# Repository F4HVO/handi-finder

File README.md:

# handi-finder
F4HVO implementation of Handi Finder.

This circuit was made in a hurry but fortunately it works.

## How to make it

- Send the gerber files to your favorite PCB factory (OSH Park, Elecrow, AllPCB, ...).
- Get the components (see BOM below)
- Assemble (hot air station or reflow oven recommended, but a frying pan and sand can do the trick)
- Then add antennas : rigid wire of 48cm on each side, between ANT1 and ANT1GND (and ANT2-ANT2GND respectively). Make a bow shape by bending the wire to form 3 edges (two of 17cm and one of 12cm).
- Have fun.

## BOM
All capacitors and resistors are 0805.

- U1 : CD4047 (smd version)
- C1 : 0.2 uF
- C2, C3, C4, C5, C6, C7 : 1nF
- C8 : 0.1 uF
- R1, R2, R3 : 10k
- D1, D2 : 1n4148 (or any switching diode, or PIN diode)
- Switch : good luck, or no switch
- SMA connector
- 9V battery (and connector)

## Remarks

- The switch package is unfamiliar, a more standard one might be better. I did not use a switch, I soldered a jumper on my assembled board.

## Release notes

### Version 1.1 :
- Change diodes package to SOD 123
- Change hole diameter to 2.6mm

### Version 1.2 :
- Fix switch connection, CD4047 was always powered on.

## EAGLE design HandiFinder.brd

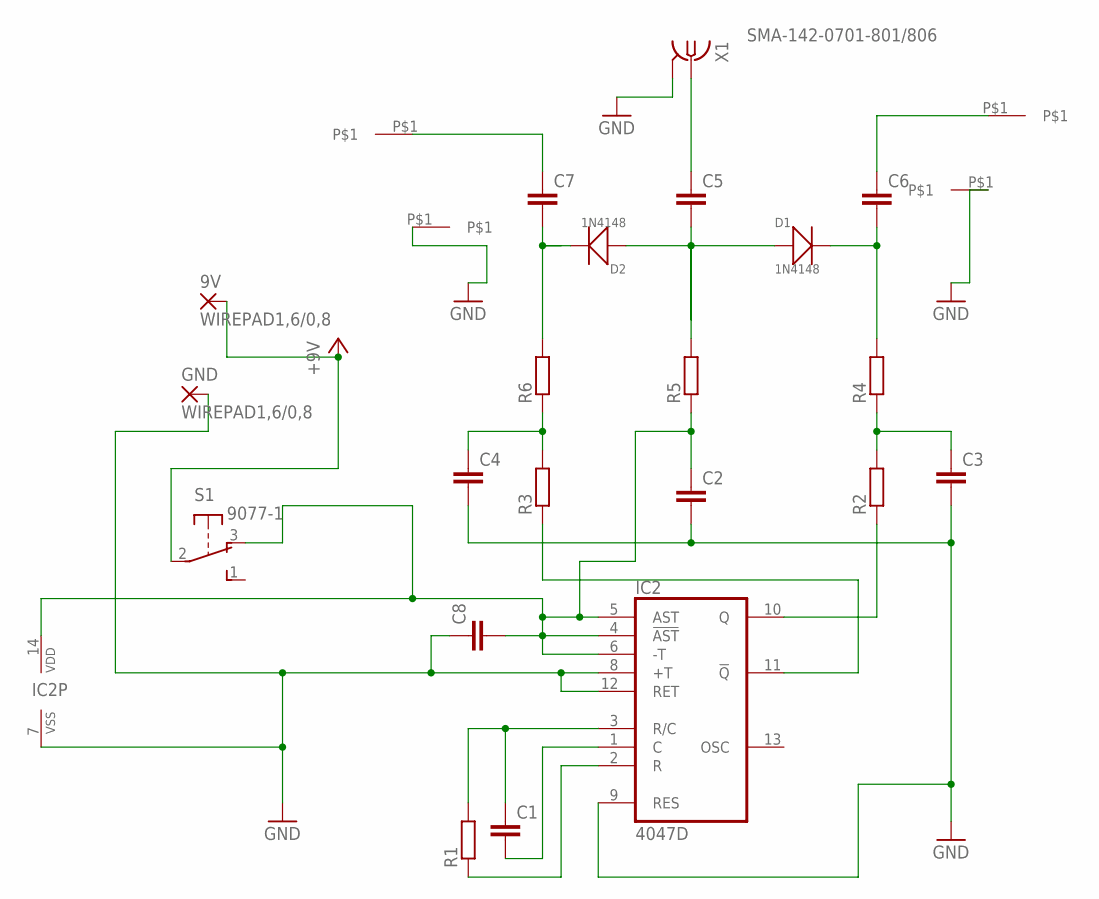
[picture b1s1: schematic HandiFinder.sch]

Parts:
9V: WIREPAD1,6/0,8; 1,6/0,8
ANT1: ANT12; 2.6MMHOLE
ANT1GND2, ANT2GND2, ANT22: WIREPAD; 2.6MMHOLE
C1, C2, C3, C4, C5, C6, C7, C8: C-EUC0805K; C0805K
D1, D2: 1N4148; SOD-123
GND: WIREPAD1,6/0,8; 1,6/0,8
IC2: 4047D; SO14
R1, R2, R3, R4, R5, R6: R-EU_R0805; R0805
S1: 9077-1
X1: SMA-142-0701-801/806; J502-ND-142-0701-801/806

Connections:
+5V: 9V.1, S1.2
GND: ANT1GND2.P$1, ANT2GND2.P$1, C2.2, C3.2, C4.2, C8.1, GND.1, IC2.7 (VSS), IC2.8 (+T), IC2.9 (RES), IC2.12 (RET), X1.G@1 (2), X1.G@2 (2), X1.G@3 (2), X1.G@4 (2)
unnamed: C1.1, IC2.3 (R/C), R1.2
unnamed: C1.2, IC2.1 (C)
unnamed: IC2.2 (R), R1.1
unnamed: C7.2, D2.-, R6.2
unnamed: C3.1, R2.2, R4.1
unnamed: C5.1, X1.1
unnamed: C4.1, R3.2, R6.1
unnamed: IC2.11 (!Q), R3.1
unnamed: IC2.10 (Q), R2.1
unnamed: C5.2, D1.+, D2.+, R5.2
unnamed: C6.2, D1.-, R4.2
unnamed: ANT1.P$1, C7.1
unnamed: ANT22.P$1, C6.1
unnamed: C2.1, C8.2, IC2.4 (!AST), IC2.5 (AST), IC2.6 (-T), IC2.14 (VDD), R5.1, S1.3 (O)

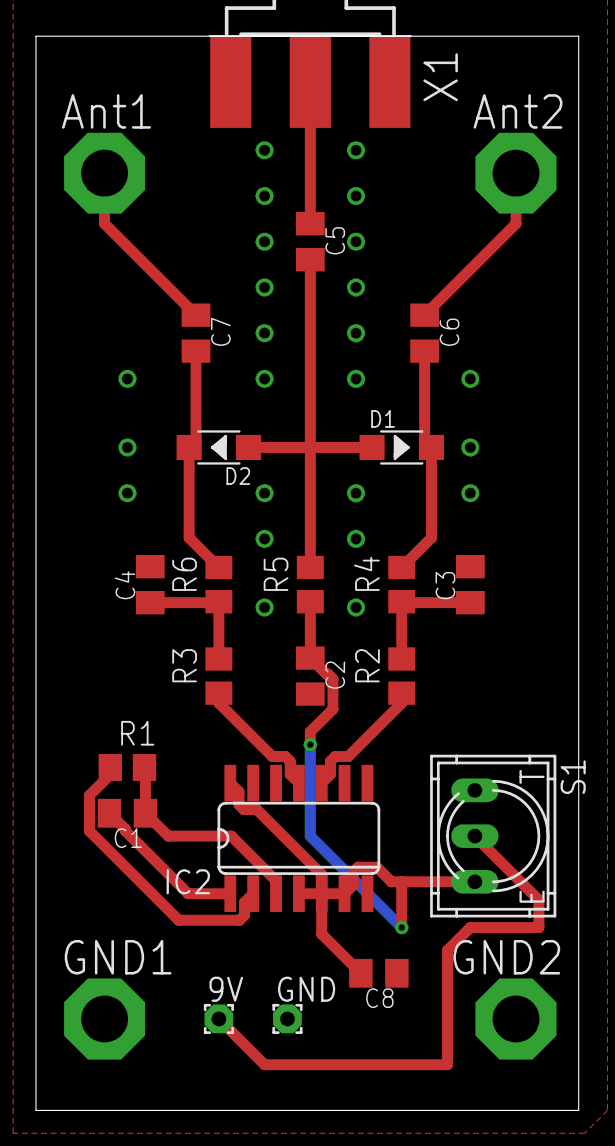
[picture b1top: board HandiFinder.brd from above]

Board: 2 copper layers, 30.1 x 59.7 mm, 25 parts (0 on the bottom side), 16 nets.

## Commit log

2019-09-03 Initial file import.
2019-09-03 Add some content to README
2019-09-03 Rotate image of board
2019-09-03 Remove unused file Switch.lbr
2019-09-10 Change hole diameter to 2.6mm to allow 2.5mm screw. Change diode footprint to SOD 123.
2019-09-10 Extend wirepad. Add gerber files.
2019-10-17 Fix switch misconnection.
